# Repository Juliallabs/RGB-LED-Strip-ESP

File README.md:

# RGB-LED-Strip-ESP
Aplicação para controlar uma Fita de LEDs RGB 5050 via internet com ESP32.

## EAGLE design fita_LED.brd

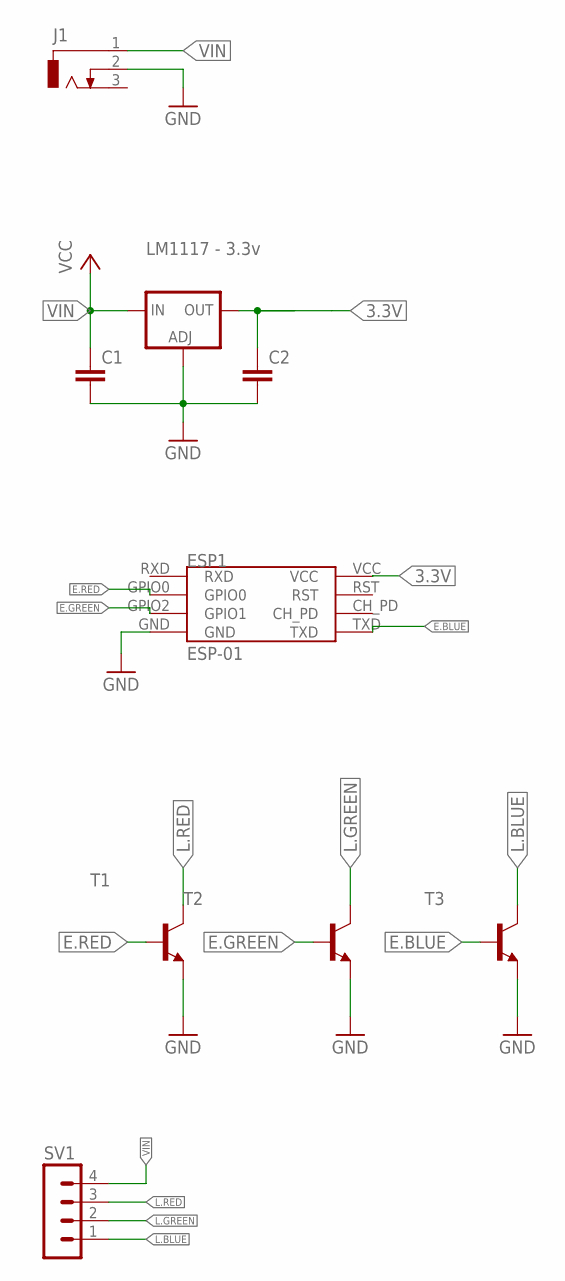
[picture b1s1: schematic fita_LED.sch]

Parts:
C1, C2: C-EUC0805; C0805
ESP1: ESP-01
IC1: LM1117 - 3.3v; SOT223
J1: DCJ0303
SV1: MA04-1
T1, T2, T3: BC817-16-NPN-SOT23-BEC; SOT23-BEC

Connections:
3.3V: C2.1, ESP1.VCC, IC1.4 (OUT)
E.BLUE: ESP1.TXD, T3.B
E.GREEN: ESP1.GPIO2 (GPIO1), T2.B
E.RED: ESP1.GPIO0, T1.B
GND: C1.2, C2.2, ESP1.GND, IC1.1 (ADJ), J1.2, T1.E, T2.E, T3.E
L.BLUE: SV1.1, T3.C
L.GREEN: SV1.2, T2.C
L.RED: SV1.3, T1.C
VIN: C1.1, IC1.3 (IN), J1.1, SV1.4

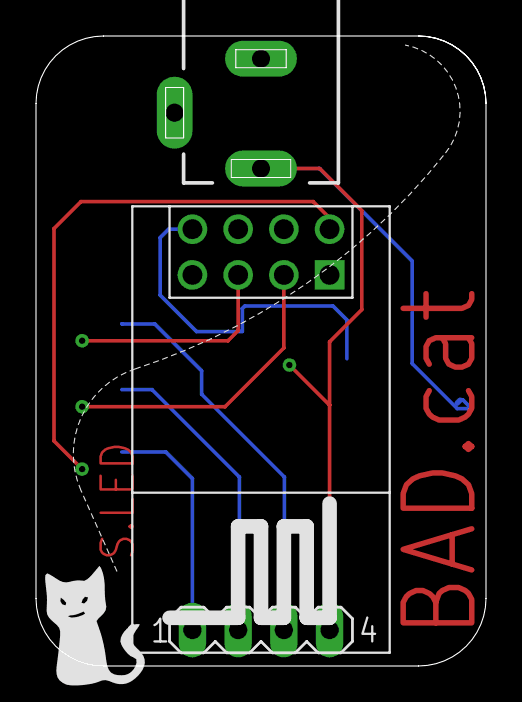
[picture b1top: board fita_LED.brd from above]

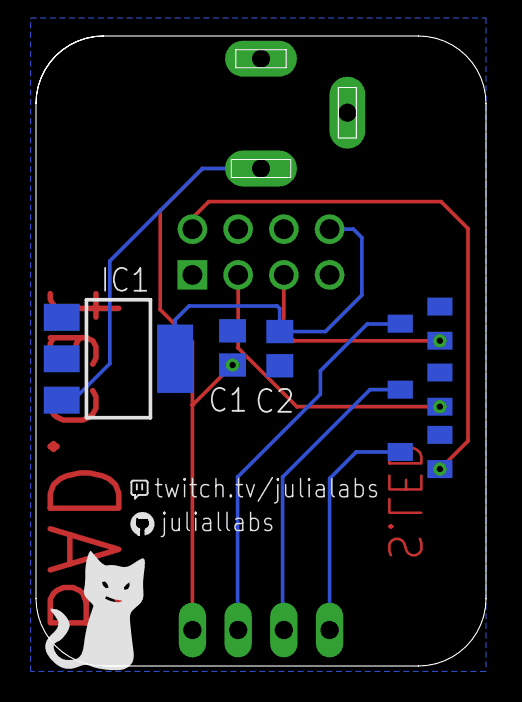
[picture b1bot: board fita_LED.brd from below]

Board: 2 copper layers, 25.0 x 35.0 mm, 9 parts (6 on the bottom side), 9 nets.

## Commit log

2021-07-22 init
2021-08-01 atualização OTA/IOT
2021-09-16 atualizacao de codigo e esquematico
